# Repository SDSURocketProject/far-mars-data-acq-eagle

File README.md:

# far-mars-dpm-pcb
Dynamic Battery and System Power Manager
* Designed for 3S Lipos
* Manages power between battery, systems, and a DC input. 
* Development for this PCB is currently on hold

## The Board

* Unfinsihed

## Bill of Materials

* Unfinished

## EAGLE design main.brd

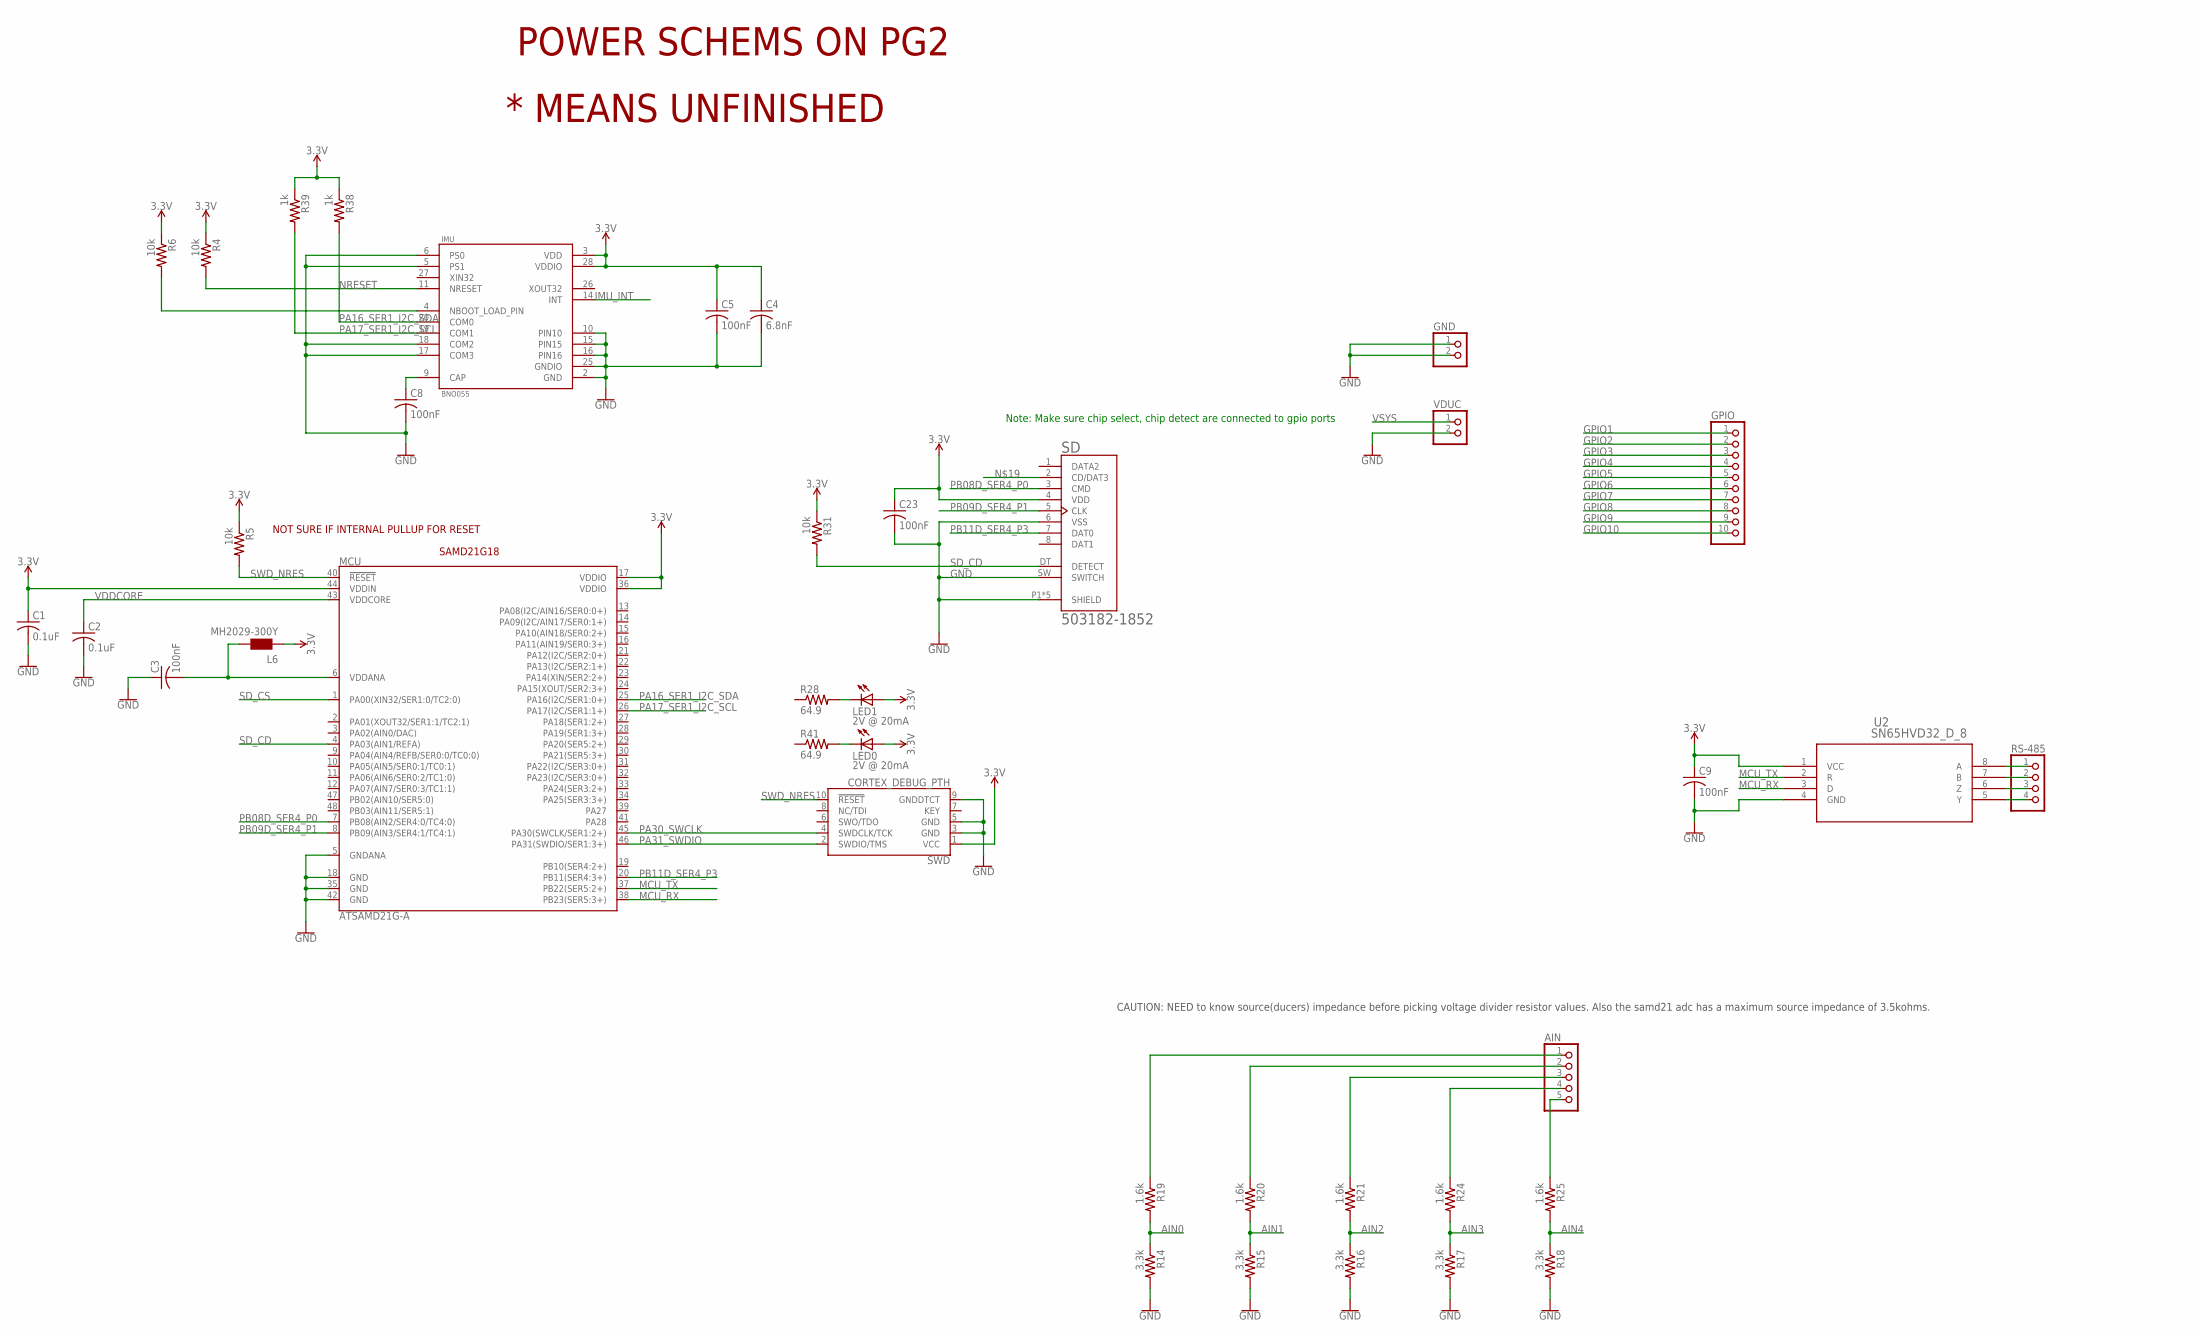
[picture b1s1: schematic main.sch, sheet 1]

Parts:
AIN: PINHD-1X5; 1X05
C1, C2: 0.1uF; C0603
C3, C5, C8, C9, C23: 100nF; C0603
C4: 6.8nF; C0603
GND: PINHD-1X2; 1X02
GPIO: PINHD-1X10; 1X10
IMU: BNO055; LGA28R50P4X10_380X520X100
L6: MH2029-300Y; 0805
LED0, LED1: 2V @ 20mA; CHIPLED_0603
MCU: ATSAMD21G-A; TQFP-48
R4, R5, R6, R31: 10k; R0603
R14, R15, R16, R17, R18: 3.3k; R0603
R19, R20, R21, R24, R25: 1.6k; R0603
R28, R41: 64.9; R0603
R38, R39: 1k; R0603
RS-485: PINHD-1X4; 1X04
SD: 503182-1852; MOLEX_503182-1852
SWD: CORTEX_DEBUG_PTH; 2X5-PTH-1.27MM
U2: SN65HVD32_D_8; D8
VDUC: PINHD-1X2; 1X02

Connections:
3.3V: C1.1, C4.1, C5.1, C9.1, C23.1, IMU.3 (VDD), IMU.28 (VDDIO), L6.1, LED0.A, LED1.A, MCU.17 (VDDIO), MCU.36 (VDDIO), MCU.44 (VDDIN), R4.1, R5.1, R6.1, R31.1, R38.1, R39.1, SD.4 (VDD), SWD.1 (VCC), U2.1 (VCC); also elsewhere on the board
AIN0: R14.1, R19.2
AIN1: R15.1, R20.2
AIN2: R16.1, R21.2
AIN3: R17.1, R24.2
AIN4: R18.1, R25.2
GND: C1.2, C2.2, C3.1, C4.2, C5.2, C8.2, C9.2, C23.2, GND.1, GND.2, IMU.2 (GND), IMU.5 (PS1), IMU.6 (PS0), IMU.10 (PIN10), IMU.15 (PIN15), IMU.16 (PIN16), IMU.17 (COM3), IMU.18 (COM2), IMU.25 (GNDIO), MCU.5 (GNDANA), MCU.18 (GND), MCU.35 (GND), MCU.42 (GND), R14.2, R15.2, R16.2, R17.2, R18.2, SD.6 (VSS), SD.P1 (SHIELD), SD.P2 (SHIELD), SD.P3 (SHIELD), SD.P4 (SHIELD), SD.P5 (SHIELD), SD.SW (SWITCH), SWD.3 (GND), SWD.5 (GND), SWD.9 (GNDDTCT), U2.4 (GND), VDUC.2; also elsewhere on the board
GPIO1: GPIO.1
GPIO2: GPIO.2
GPIO3: GPIO.3
GPIO4: GPIO.4
GPIO5: GPIO.5
GPIO6: GPIO.6
GPIO7: GPIO.7
GPIO8: GPIO.8
GPIO9: GPIO.9
GPIO10: GPIO.10
IMU_INT: IMU.14 (INT)
MCU_RX: MCU.38 (PB23(SER5:3+)), U2.3 (D)
MCU_TX: MCU.37 (PB22(SER5:2+)), U2.2 (R)
unnamed: AIN.2, R20.1
unnamed: C3.2, L6.2, MCU.6 (VDDANA)
unnamed: AIN.3, R21.1
unnamed: AIN.4, R24.1
unnamed: AIN.5, R25.1
unnamed: RS-485.1, U2.8 (A)
unnamed: LED0.C, R41.2
unnamed: AIN.1, R19.1
unnamed: C8.1, IMU.9 (CAP)
unnamed: RS-485.2, U2.7 (B)
unnamed: RS-485.3, U2.6 (Z)
unnamed: RS-485.4, U2.5 (Y)
unnamed: IMU.4 (NBOOT_LOAD_PIN), R6.2
unnamed: LED1.C, R28.2
NRESET: IMU.11 (NRESET), R4.2
PA16_SER1_I2C_SDA: IMU.20 (COM0), MCU.25 (PA16(I2C/SER1:0+)), R38.2
PA17_SER1_I2C_SCL: IMU.19 (COM1), MCU.26 (PA17(I2C/SER1:1+)), R39.2
PA30_SWCLK: MCU.45 (PA30(SWCLK/SER1:2+)), SWD.4 (SWDCLK/TCK)
PA31_SWDIO: MCU.46 (PA31(SWDIO/SER1:3+)), SWD.2 (SWDIO/TMS)
PB08D_SER4_P0: MCU.7 (PB08(AIN2/SER4:0/TC4:0)), SD.3 (CMD)
PB09D_SER4_P1: MCU.8 (PB09(AIN3/SER4:1/TC4:1)), SD.5 (CLK)
PB11D_SER4_P3: MCU.20 (PB11(SER4:3+)), SD.7 (DAT0)
SD_CD: MCU.4 (PA03(AIN1/REFA)), R31.2, SD.DT (DETECT)
SD_CS: MCU.1 (PA00(XIN32/SER1:0/TC2:0))
SWD_NRES: MCU.40 (!RESET!), R5.2, SWD.10 (!RESET)
VDDCORE: C2.1, MCU.43 (VDDCORE)
VSYS: VDUC.1; also elsewhere on the board

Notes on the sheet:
SAMD21G18
POWER SCHEMS ON PG2
* MEANS UNFINISHED
NOT SURE IF INTERNAL PULLUP FOR RESET
Note: Make sure chip select, chip detect are connected to gpio ports
CAUTION: NEED to know source(ducers) impedance before picking voltage divider resistor values. Also the samd21 adc has a maximum source impedance of 3.5kohms.

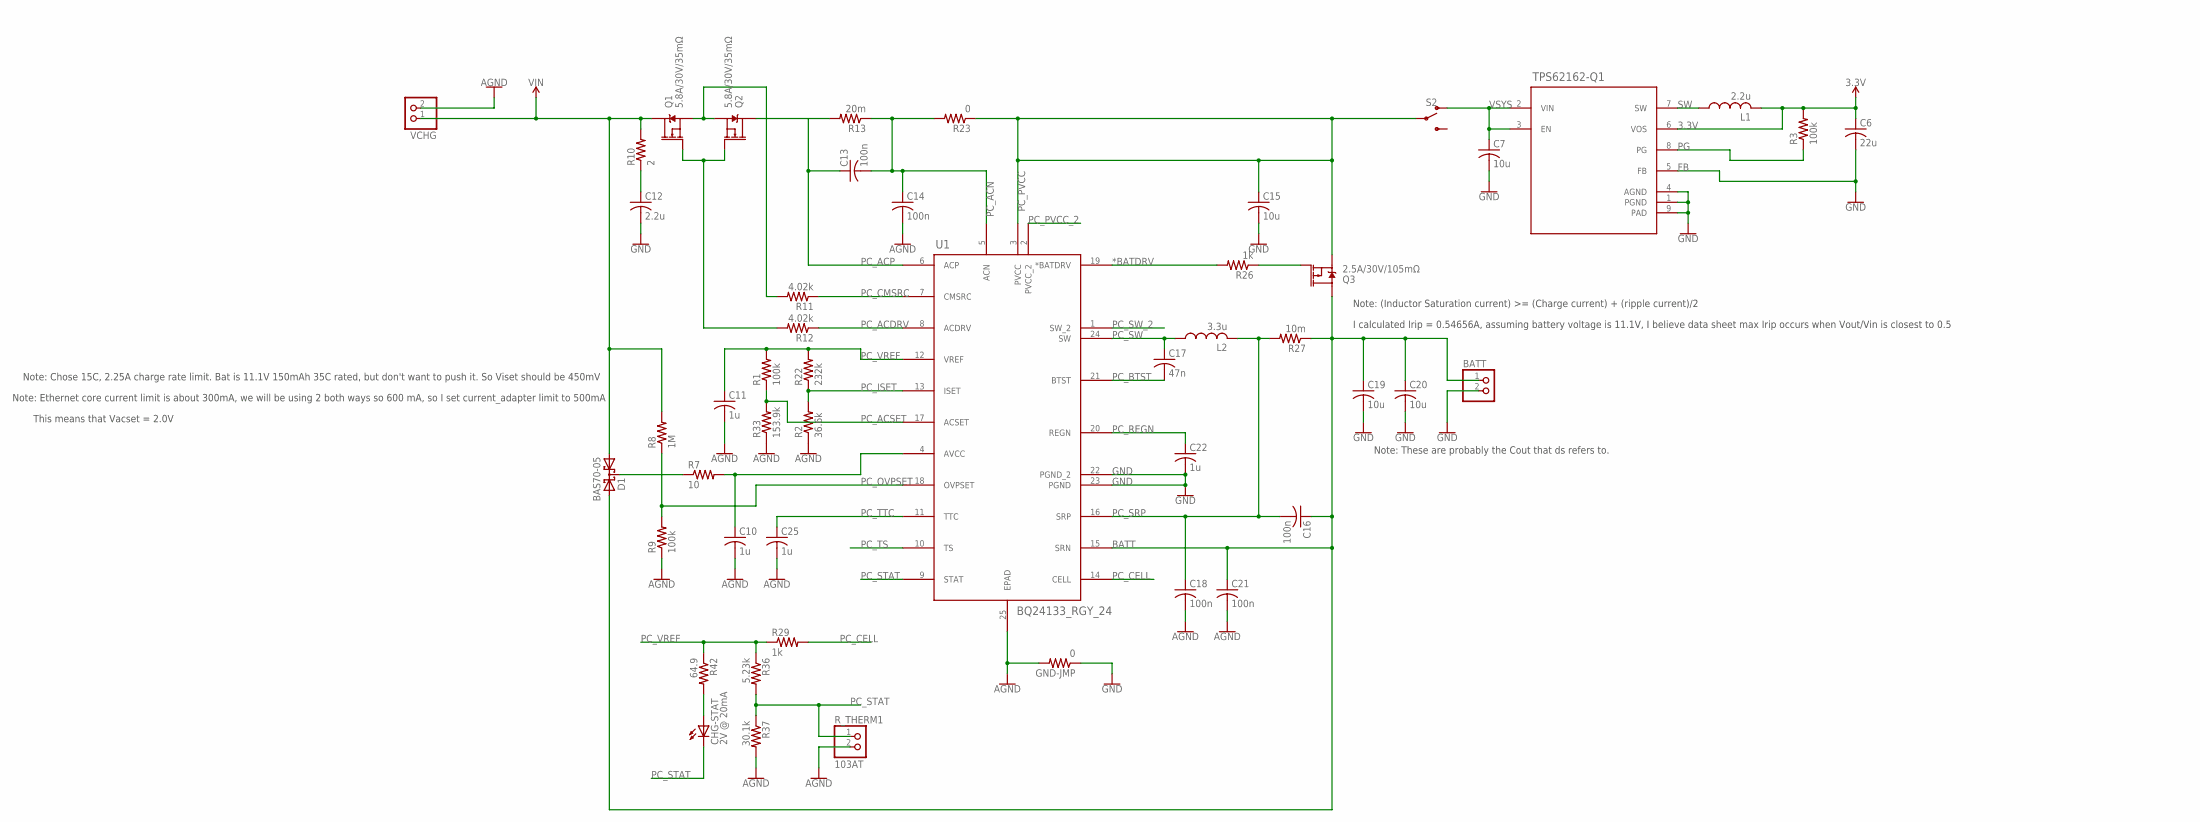
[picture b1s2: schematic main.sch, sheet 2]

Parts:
BATT: PINHD-1X2; 1X02
C6: 22u; C0603
C7: 10u; C1206
C10, C11, C22, C25: 1u; C0603
C12: 2.2u; C0603
C13, C14, C16, C18, C21: 100n; C0603
C15, C19, C20: 10u; C0603
C17: 47n; C0603
CHG-STAT: 2V @ 20mA; CHIPLED_0603
D1: BAS70-05; SOT23
GND-JMP: 0; R0603
L1: 2.2u; L2012C
L2: 3.3u; L3225M
Q1, Q2: 5.8A/30V/35mΩ; SOT23-3
Q3: 2.5A/30V/105mΩ; SOT23-3
R1, R3, R9: 100k; R0603
R2: 36.6k; R0603
R7: 10; R0603
R8: 1M; R0603
R10: 2; R0603
R11, R12: 4.02k; R0603
R13: 20m; R0603
R22: 232k; R0603
R23: 0; R0603
R26, R29: 1k; R0603
R27: 10m; R0603
R33: 153.9k; R0603
R36: 5.23k; R0603
R37: 30.1k; R0603
R42: 64.9; R0603
R_THERM1: 103AT; 1X02
S2: SWITCH-SPDT-SMD-AYZ0202; SWITCH_DPDT_SMD_AYZ0202
TPS62162-Q1: TPS62162QDSGRQ1; DSG0008A
U1: BQ24133_RGY_24; RGY24_2P05X3P1
VCHG: PINHD-1X2; 1X02

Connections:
3.3V: C6.1, L1.2, R3.2, TPS62162-Q1.6 (VOS); also elsewhere on the board
*BATDRV: R26.2, U1.19 (*BATDRV)
AGND: C10.2, C11.2, C14.2, C18.2, C21.2, C25.2, GND-JMP.2, R2.1, R9.1, R33.1, R37.2, R_THERM1.2, U1.25 (EPAD), VCHG.2; also elsewhere on the board
BATT: BATT.1, C16.1, C19.1, C20.1, C21.1, D1.2 (A2), Q3.3 (D), R27.1, U1.15 (SRN)
FB: C6.2, TPS62162-Q1.5 (FB)
GND: BATT.2, C7.2, C12.2, C15.2, C19.2, C20.2, C22.2, GND-JMP.1, TPS62162-Q1.1 (PGND), TPS62162-Q1.4 (AGND), TPS62162-Q1.9 (PAD), U1.22 (PGND_2), U1.23 (PGND); also elsewhere on the board
unnamed: Q3.1 (G), R26.1
unnamed: D1.3 (C), R7.1
unnamed: C12.1, R10.1
unnamed: Q1.2 (S), Q2.2 (S), R11.2
unnamed: Q1.1 (G), Q2.1 (G), R12.2
unnamed: C10.1, R7.2, U1.4 (AVCC)
unnamed: CHG-STAT.A, R42.2
PC_ACDRV: R12.1, U1.8 (ACDRV)
PC_ACN: C13.2, C14.1, R13.1, R23.2, U1.5 (ACN)
PC_ACP: C13.1, Q2.3 (D), R13.2, U1.6 (ACP)
PC_ACSET: R1.1, R33.2, U1.17 (ACSET)
PC_BTST: C17.2, U1.21 (BTST)
PC_CELL: R29.2, U1.14 (CELL)
PC_CMSRC: R11.1, U1.7 (CMSRC)
PC_ISET: R2.2, R22.1, U1.13 (ISET)
PC_OVPSET: R8.1, R9.2, U1.18 (OVPSET)
PC_REGN: C22.1, U1.20 (REGN)
PC_SRP: C16.2, C18.1, L2.2, R27.2, U1.16 (SRP)
PC_TTC: C25.1, U1.11 (TTC)
PC_VREF: C11.1, R1.2, R22.2, R29.1, R36.1, R42.1, U1.12 (VREF)
PG: R3.1, TPS62162-Q1.8 (PG)
SW: L1.1, TPS62162-Q1.7 (SW)
VIN: D1.1 (A1), Q1.3 (D), R8.2, R10.2, VCHG.1
VSYS: C7.1, S2.1 (O), TPS62162-Q1.2 (VIN), TPS62162-Q1.3 (EN); also elsewhere on the board

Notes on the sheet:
Note: Chose 15C, 2.25A charge rate limit. Bat is 11.1V 150mAh 35C rated, but don't want to push it. So Viset should be 450mV
Note: Ethernet core current limit is about 300mA, we will be using 2 both ways so 600 mA, so I set current_adapter limit to 500mA
This means that Vacset = 2.0V
Note: These are probably the Cout that ds refers to.
I calculated Irip = 0.54656A, assuming battery voltage is 11.1V, I believe data sheet max Irip occurs when Vout/Vin is closest to 0.5
Note: (Inductor Saturation current) >= (Charge current) + (ripple current)/2

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
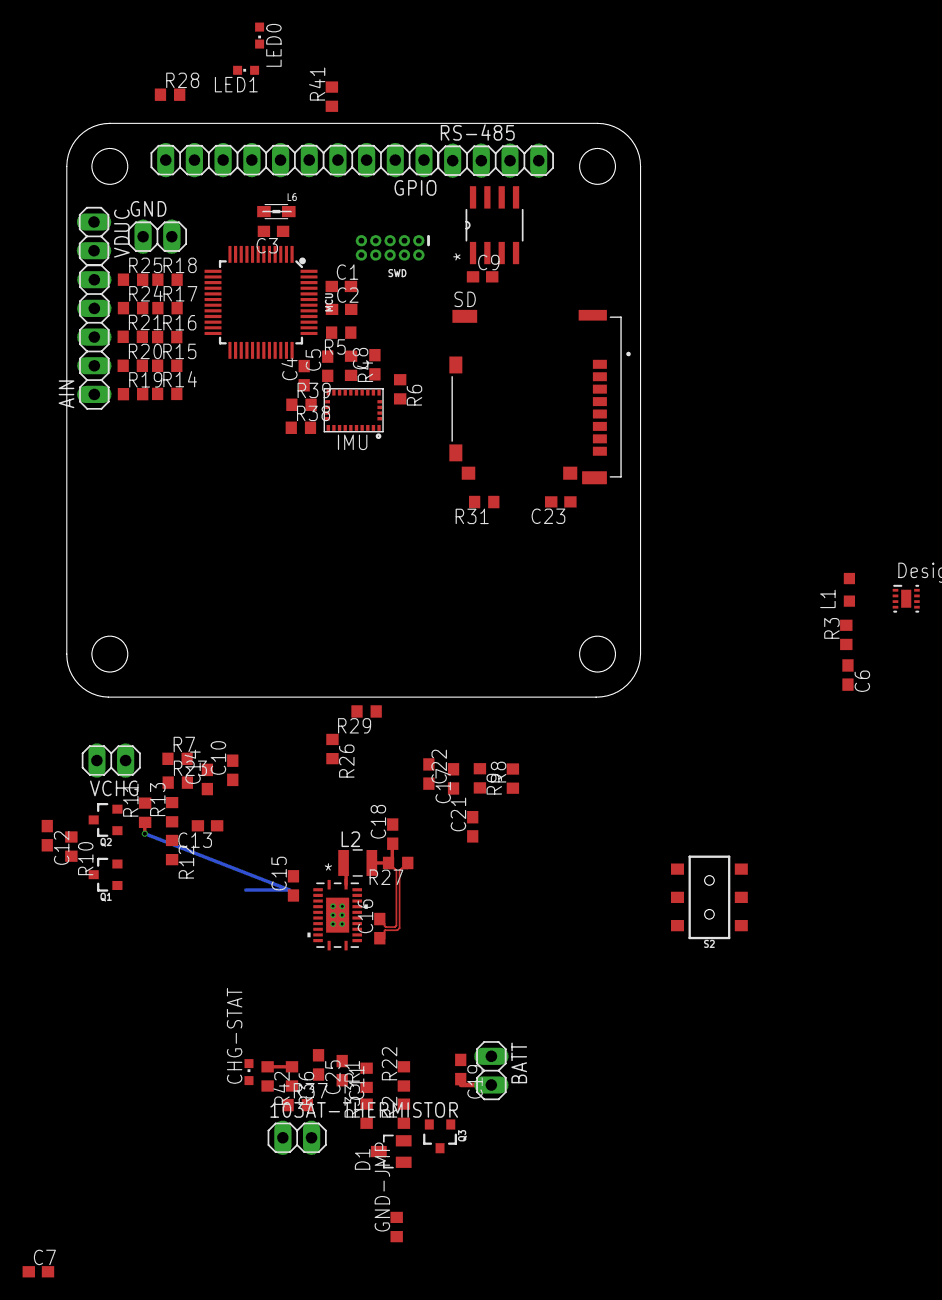
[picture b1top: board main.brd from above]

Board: 4 copper layers, 50.8 x 50.8 mm, 91 parts (0 on the bottom side), 66 nets.

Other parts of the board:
103AT-THERMISTOR: 10k; 1X02
U$1, U$2, U$3, U$4: DRILL_0.1250

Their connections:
AGND: 103AT-THERMISTOR.2; also elsewhere on the board

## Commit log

2018-01-03 Added some nets to schematic
2018-01-03 Added brd file
    Autogenerated footprint positions, they need to be moved
2018-01-03 Testing atrributes
2018-01-03 Revert "Testing atrributes"
    This reverts commit 77f31cc4e45a7ef5c7aa64ba64ed9b769b4784e2.
2018-01-03 Added some labels to Schematic
2018-01-03 Added Attributes
2018-01-05 Added SD, AIO, and Valve State IO
    Added Analog IO ports along with modified voltage dividers.
    Added valve state ports, and a connected state jumper.
    Added SD card, and conencted it SPI bus, unsure what CD pins are, and if RSV pings need to be connected at all.
2018-01-05 Added IMU and Battery Controller
    Battery Controller IC may be wrong
2018-01-07 Added IMU Configuration
    Added Imu Nets
    Removed AIO and GPIO Net assignments for now, since they can go anywhere
    Named SD CARD SPI pins accordingly, these should be final
2018-01-08 Added Some notes
2018-01-10 Added lib folder, added charge controller schematic
    Almost finished naming nets and component values.
2018-01-10 Added and removed some i/o
2018-01-10 Started board design
    Still need to add I2C, GPIO, and AIO nets in schematic. Need to also add status leds.
2018-01-11 Assembled alot of the board layout
    Mostly charge controller elements
2018-01-12 Finished board Layout
    First attempt at a board layout for the schematic, most likley not final.
2018-01-15 Reworked Layout, added thermocouple ics
    Second attempt at a board layout, more balanced spacing.
2018-01-19 Some fixes, layout additions
2018-01-20 More layout additions
2018-01-20 Finished 2nd layout
    Still needs a few error corrections and status leds where possible.
2018-01-20 Fixed some air wires
2018-01-21 A few spacing adjustments
2018-01-22 Updated 3.3reg values, fixed led resitor, added one led to mcu
2018-01-23 Fixed 3.3v reg
2018-01-24 Added new Battery Controller Model
2018-01-27 Removed Thermocouple ICs, Riped up everything, added a few more gpio pins
2018-01-28 Updated Power Schematics
    Attatched to new model, better represents power controller datasheet.
2018-01-29 iMAGE TEST
    ImAGE
2018-01-29 Removing test
2018-01-31 Seperated AGND and PGND, set a few current limiting pin configs, misc schematic changes
2018-02-02 Just combined accidental "branches"
    Includes last commit and some layout progress.
2018-02-02 Added leds, switched out SD card symbol and footprint
    Couldn't find old footprint model # to actually order the part.
2018-02-04 Routing
    Working on finishing it up
2018-02-04 Power
    Ther are a few more things that I need to fix with power but this is the first prototype. I need to figure our how far away can D1 be from the battery imput before finilazing everything
2018-02-05 Some layout stuff, package changes
2018-02-07 Seperated grounds, added pullup to cell pin
2018-02-08 Set adc voltage divider values
    Used 100ohm output impedance of ducers and 3.5kohm limit in samd21 datasheet to arrive at the vdiv resistor values.
2018-02-08 Routing
    Need to choose L and sizes for caps and res
2018-02-08 Still need to change pad sizes
2018-02-09 More value changes, package updates needed
2018-02-20 layout overlook
    Done

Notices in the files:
parts and their libraries:
SparkFun-IC-Microcontroller: Licensing: Creative Commons ShareAlike 4.0 International - https://creativecommons.org/licenses/by-sa/4.0
